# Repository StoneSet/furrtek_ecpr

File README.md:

# EPAR EMITTER HACK

## The Eagle project of the epar project + and modified firmware

**(c) Found the entire project here : http://furrtek.free.fr/?a=epar**

## For futher

As we know, only 350 cities (minimum), have been equipped with this system, (which makes 10% of the total cities in France in 2014). To have this famous cities code which is coded on 8 bits (so 255 possibilities), it is necessary to scan the frequencies 31MHz to 32MHz, which is tedious, this repo proposes to you a "brut-force", the program has been modified so that the 255 possibilities are tested. Once you have the code you can directly inform it in the remote control, it will go faster. This is just the theory, I have not tried it yet, but I would update this readme as soon as I have some pretty big breakthroughs.

## Included:

- All needed files to modify the project
- BOM (see in /pcb/)
- 🚧 Modified firmware (see in /firmware/) in WIP

## To use it :

1. Buy the pcb then solder every composants.
2. Flash the Atmega8 with *eparremote.hex* with these fuses :

- Low: *0xE4*, High: *0xD9*
## Some img's :

### To dot it, you will need :

| Components | list |
|--|--|
| x1 Atmega8 | x1 78L05 regulator |
| x1 10k potentiometer | x4 12mm switch |
| x1 0802 screen | x1 AD9850 |
| x1 10k resistor | x1 47uF capacitor |
| x1 100uH coil | x1 Green led |
| x1 1nF capacitor | x1 10nF capacitor |
| x1 BFR96 | x1 47k resistor |
| x1 SPDT switch | x1 FM antenna |
| x1 9v clip | x1 1N4001 diode |

Tested, it will work perfectly !

#

(c) @furrtek & @StoneSet & @lefuturiste - http://furrtek.free.fr/?a=esl - http://stoneset.github.io/ (2019)

plz do not steal, i'm not the owner of this project, i'm only the owner of this pcb. Have fun !

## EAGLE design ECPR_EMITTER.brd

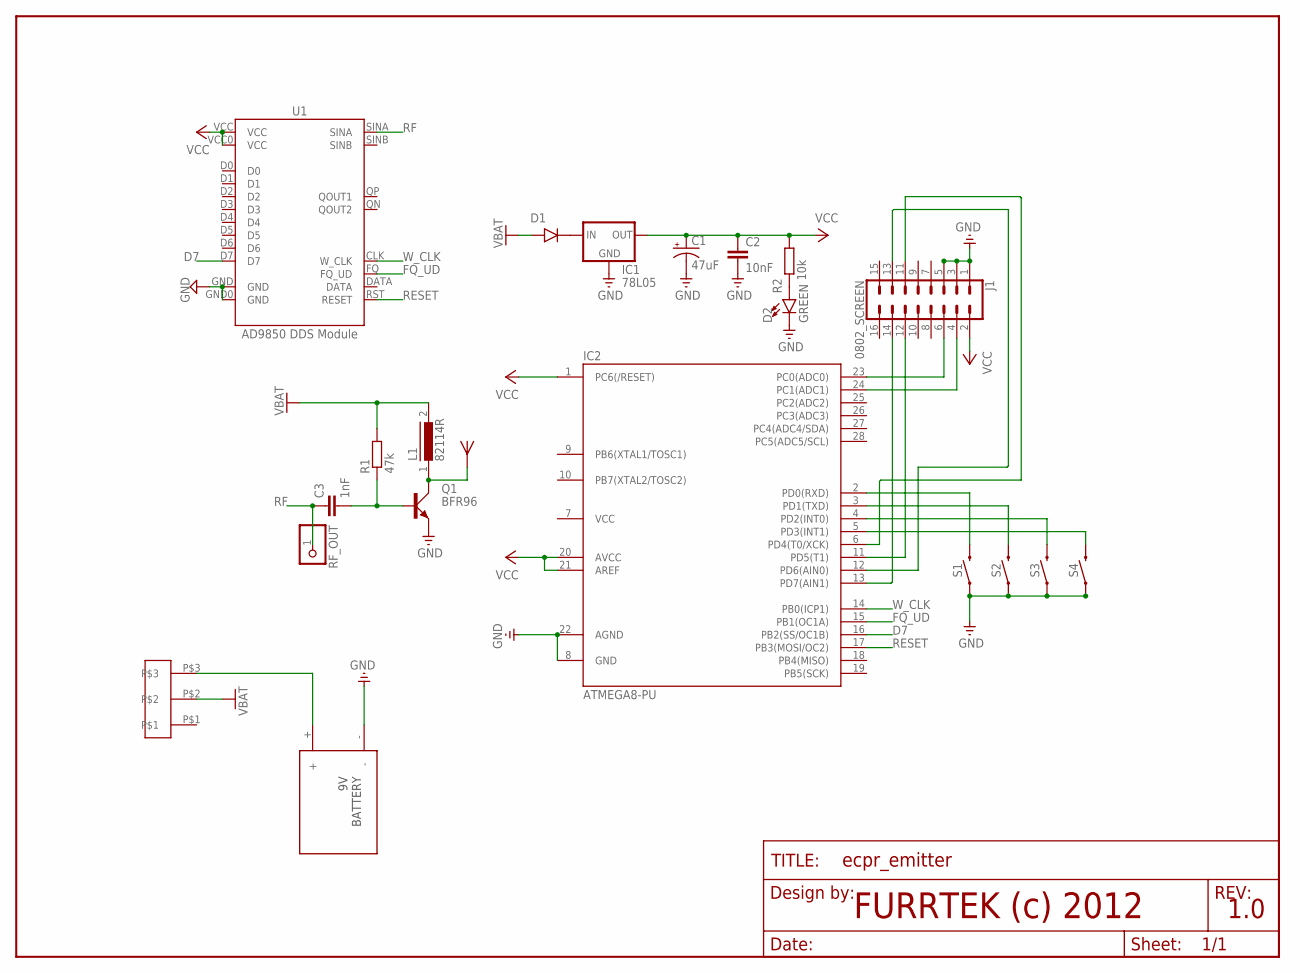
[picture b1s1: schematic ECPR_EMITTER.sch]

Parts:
C1: 47uF; CPOL-RADIAL-10UF-25V
C2: 10nF; CAP-PTH-10MM
C3: 1nF; C5B3
D1: 1N4001; DO41-10
D2: GREEN; LED_3MM-NS
FRAME1: FRAME-LETTERNO_PACKAGE; DUMMY
IC1: 78L05; 78XXL
IC2: ATMEGA8-PU; DIL28-3
J1: 0802_SCREEN; 2X8
L1: 82114R
Q1: BFR96; SOT37
R1: 47k; 0207/7
R2: 10k; 0207/7
RF_OUT: PINHD-1X1; 1X01
S1, S2, S3, S4: MOMENTARY-SWITCH-SPST-PTH-12MM; TACTILE_SWITCH_PTH_12MM
U1: AD9850 DDS Module; DDS_AD9850
U$1: ANT.; ANTENNA
U$2: PACKAGESWITCH; SLIDESWITCH
U$3: BAT

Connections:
D7: IC2.16 (PB2(SS/OC1B)), U1.D7
FQ_UD: IC2.15 (PB1(OC1A)), U1.FQ (FQ_UD)
GND: C1.2 (-), C2.2, D2.K (C), IC1.GND, IC2.8 (GND), IC2.22 (AGND), J1.1, J1.3, J1.5, Q1.2 (E), S1.1, S2.1, S3.1, S4.1, U1.GND, U1.GND0 (GND), U$3.-
unnamed: D1.C (CATHODE), IC1.IN
unnamed: C3.2, Q1.3 (B), R1.1
unnamed: IC2.2 (PD0(RXD)), S1.3 (2)
unnamed: IC2.3 (PD1(TXD)), S2.3 (2)
unnamed: IC2.4 (PD2(INT0)), S3.3 (2)
unnamed: IC2.5 (PD3(INT1)), S4.3 (2)
unnamed: L1.1, Q1.1 (C), U$1.ANT
unnamed: IC2.24 (PC1(ADC1)), J1.4
unnamed: IC2.23 (PC0(ADC0)), J1.6
unnamed: IC2.13 (PD7(AIN1)), J1.14
unnamed: IC2.11 (PD5(T1)), J1.12
unnamed: U$2.P$3, U$3.+
unnamed: IC2.12 (PD6(AIN0)), J1.13
unnamed: IC2.6 (PD4(T0/XCK)), J1.11
unnamed: D2.A, R2.1
RESET: IC2.17 (PB3(MOSI/OC2)), U1.RST (RESET)
RF: C3.1, RF_OUT.1, U1.SINA
VBAT: D1.A (ANODE), L1.2, R1.2, U$2.P$2
VCC: C1.1 (+), C2.1, IC1.OUT, IC2.1 (PC6(/RESET)), IC2.7 (VCC), IC2.20 (AVCC), IC2.21 (AREF), J1.2, R2.2, U1.VCC, U1.VCC0 (VCC)
W_CLK: IC2.14 (PB0(ICP1)), U1.CLK (W_CLK)

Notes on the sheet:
FURRTEK (c) 2012
1.0

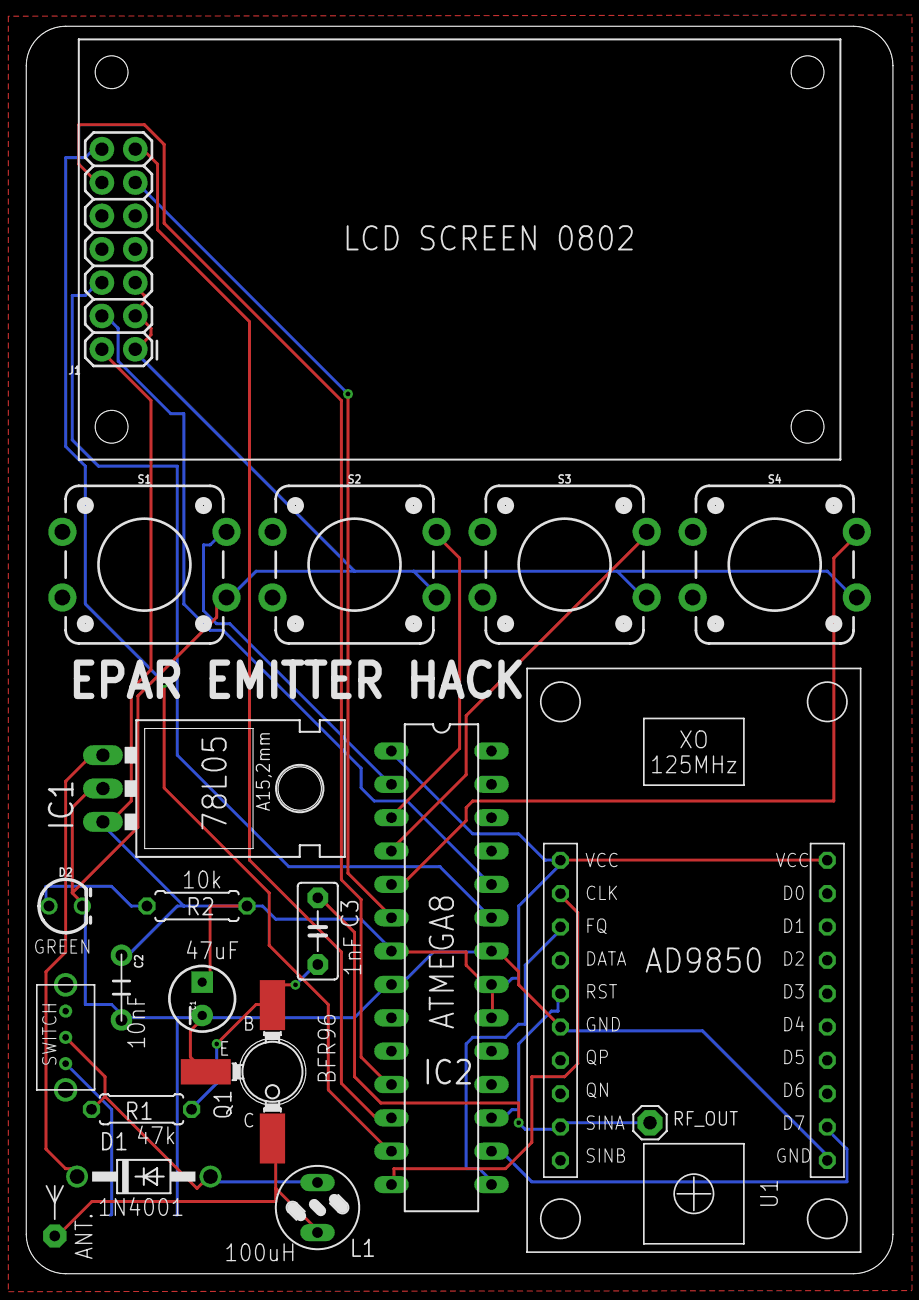
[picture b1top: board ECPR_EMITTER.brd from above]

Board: 2 copper layers, 66.0 x 95.0 mm, 22 parts (1 on the bottom side), 23 nets.

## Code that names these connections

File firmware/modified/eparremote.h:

#define PULLUPS 0b00001111

void com(uint8_t command);
void disp();
void cur_rel();
void cur_freq();
void cur_span();
void cur_code();
void cur_zone();
void wrt(const uint8_t *FlashLoc);
void EPAR_TX(uint8_t citycode, uint8_t zone, uint8_t relay, uint8_t state, uint8_t reverse, uint8_t rep);
void wrtr(char *cbuf);
void wrtc(char chr);
void Up();
void Down();
uint8_t hex(uint8_t num);

#define ZONE_A 0
#define ZONE_B 1
#define ZONE_C 2
#define ZONE_TP 3

#define RELAY1	1
#define RELAY2  0

#define OPEN 0
#define CLOSED 1

#define NORMAL 0
#define REVERSE 1

#define REPEAT 26

#define FREQ_MAX 40
#define FREQ_MIN 20

#define ECART_MAX 1
#define ECART_MIN 0.001

#define POWERDOWN 4

#define AD9850_W_CLK	PB0
#define AD9850_FQ_UD	PB1
#define AD9850_D7		PB2
#define AD9850_RESET	PB3

#define E	PC0
#define RS	PC1

enum MENUT {MENU_FREQ,MENU_SPAN,MENU_REL,MENU_CODE,MENU_ZONE,MENU_XMIT};

#define MENU_FIRST MENU_FREQ
#define MENU_LAST MENU_XMIT

const double power[6];

char test[8];

uint8_t editing,selected;
uint8_t reli,bitedit,digitedit;

uint8_t relay[2],menu;
double	fr;
uint8_t citycode;
uint8_t zone;
double ec;

uint8_t EEcode;
uint8_t EEzone;
uint8_t EEmenu;
uint32_t EEfr;
uint32_t EEec;

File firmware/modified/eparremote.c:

/*
Telecommande EPAR v1.1
07/10/2012 CC by Furrtek
ATMega8 8Mhz RC
*/

#define F_CPU 8000000UL

#include <avr/io.h>
#include <avr/interrupt.h>
#include <util/delay.h>
#include <stdlib.h>
#include <inttypes.h>
#include <avr/pgmspace.h>
#include <avr/eeprom.h>

#include "special.h"
#include "lcd.h"
#include "eparremote.h"
#include "navig.h"

typedef void (*FuncPtr)();
FuncPtr FPtr;

uint8_t editing=0;		// Bool valeur en edition
uint8_t selected=0;		// Bool chiffre choisi
uint8_t reli=0;			// # relais en edition
uint8_t bitedit=0;		// # bit en edition
uint8_t digitedit=0;	// # chiffre en edition

uint8_t relay[2] = {0,0};	// Etat relais
uint8_t menu = MENU_CODE;	// Menu (au demarrage)
double fr;					// Valeur frequence centrale (MHz)
double ec;					// Valeur ecart frequence (MHz)
uint8_t citycode;
uint8_t zone;

uint8_t EEMEM EEcode;		// Sauvegardes en EEPROM
uint8_t EEMEM EEzone;
uint8_t EEMEM EEmenu;
uint32_t EEMEM EEfr;
uint32_t EEMEM EEec;

const uint8_t fwa[] PROGMEM = "TLC EPAR";	// Splash pour se la peter
const uint8_t fwb[] PROGMEM = "Ver. 1.1";
const uint8_t fwc[] PROGMEM = "Furrtek\"";
const uint8_t fwd[] PROGMEM = "07/10/12";

// Table de handlers pour les menus
const FuncPtr FTableEditing[] PROGMEM = {FE_DIGIT,FE_DIGIT,FE_REL,FE_CODE,FE_ZONE,FE_XMIT};
const FuncPtr FTableChoose[] PROGMEM = {FC_FREQ,FC_SPAN,FC_REL,FC_CODE,FC_ZONE,FC_XMIT};
const FuncPtr FTableLeftEditing[] PROGMEM = {FLE_FREQ,FLE_SPAN,FLE_REL,FLE_CODE,FLE_ZONE,FLE_XMIT};
const FuncPtr FTableRightEditing[] PROGMEM = {FRE_FREQ,FRE_SPAN,FRE_REL,FRE_CODE,FRE_ZONE,FRE_XMIT};
const FuncPtr FTableDisp[] PROGMEM = {FD_FREQ,FD_SPAN,FD_REL,FD_CODE,FD_ZONE,FD_XMIT};
const FuncPtr FTableSave[] PROGMEM = {FS_FREQ,FS_SPAN,FS_REL,FS_CODE,FS_ZONE,FS_XMIT};

const double power[6] = {0.0001,0.001,0.01,0.1,1,10};	// Puissances de 10

void disp() {
	// MAJ affichage LCD
	FPtr=(FuncPtr)pgm_read_word(&FTableDisp[menu]);
	FPtr();
}

int main(void) {
	WDTCR = (1<<WDCE) | (1<<WDE);	// Watchdog off (dangereux)
	WDTCR = 0x00;

	DDRB = 0b00001111;	// Outputs vers AD9850
	DDRD = 0b11110000;	// Data LCD
	DDRC = 0b00000011;	// Control LCD

	PORTD = 0b00100000 | PULLUPS;	// Mode 8 bits
	_delay_us(100);
	PORTC |= _BV(E);
	_delay_us(100);
	PORTC &= ~_BV(E);
	_delay_us(100);

	com(0b00101000);		// 2 lignes
	com(0b00000001);		// Clear
	com(0b00000010);		// Home
	com(0b00001100);		// Ecran on, cursor off, blink off

	com(0b10000000);		// Ligne 1
	wrt(fwa);
	com(0b11000000);		// Ligne 2
	wrt(fwb);

	_delay_ms(1000);

	com(0b10000000);		// Ligne 1
	wrt(fwc);
	com(0b11000000);		// Ligne 2
	wrt(fwd);

	_delay_ms(1000);

	PORTB = _BV(AD9850_RESET);	// Init mode serie AD9850
	_delay_ms(100);
	PORTB = 0;
	_delay_ms(100);

	PORTB = _BV(AD9850_W_CLK);
	_delay_ms(1);
	PORTB = 0;
	_delay_ms(1);

	PORTB = _BV(AD9850_FQ_UD);
	_delay_ms(1);
	PORTB = 0;
	_delay_ms(1);

	update(0,POWERDOWN);	// DDS au dodo

	// Recup sauvegarde EEPROM + sanitizing
	//menu = eeprom_read_byte(&EEmenu);
	//if (menu > MENU_LAST) menu = MENU_FIRST;
	citycode = eeprom_read_byte(&EEcode);
	zone = eeprom_read_byte(&EEzone);
	if (zone > 3) zone = 3;

	eeprom_read_block((void*)&ec, (const void*)&EEec, sizeof(double));
	if ((((*(uint32_t*)&ec) & 0x7fffffff) > 0x7f800000)||(ec < ECART_MIN)||(ec > ECART_MAX)) ec = 0.003;
	eeprom_read_block((void*)&fr, (const void*)&EEfr, sizeof(double)); 
	if ((((*(uint32_t*)&fr) & 0x7fffffff) > 0x7f800000)||(fr < FREQ_MIN)||(fr > FREQ_MAX)) fr = 31;

	disp();

	for (;;) {
		while ((PIND & PULLUPS) == PULLUPS) {};
		_delay_ms(50);
		if (!bit_is_set(PIND,PD0)) {
			// Gauche
			while(!bit_is_set(PIND,PD0)) {};
			if (editing) {
				// Modif valeur
				FPtr=(FuncPtr)pgm_read_word(&FTableLeftEditing[menu]);
				FPtr();
			} else {
				// Menu precedent
				if (menu == MENU_FIRST) {
					menu = MENU_LAST;
				} else {
					menu--;
				}
				disp();
			}
		} else if (!bit_is_set(PIND,PD3)) {
			// Droite
			while(!bit_is_set(PIND,PD3)) {};
			if (editing) {
				// Modif valeur
				FPtr=(FuncPtr)pgm_read_word(&FTableRightEditing[menu]);
				FPtr();
			} else {
				// Menu suivant
				if (menu == MENU_LAST) {
					menu = MENU_FIRST;
				} else {
					menu++;
				}
				disp();
			}
		} else if (!bit_is_set(PIND,PD1)) {
			// Edition
			while(!bit_is_set(PIND,PD1)) {};
			if (editing) {
				// Modif valeur
				FPtr=(FuncPtr)pgm_read_word(&FTableEditing[menu]);
				FPtr();
			} else {
				// Selection valeur
				eeprom_write_byte(&EEmenu,menu);
				editing = 1;
				digitedit = 0;
				FPtr=(FuncPtr)pgm_read_word(&FTableChoose[menu]);
				FPtr();
			}
		} else if (!bit_is_set(PIND,PD2)) {
			// Validation
			while(!bit_is_set(PIND,PD2)) {};
			editing = 0;
			selected = 0;
			com(0b00001100);		// blink et cursor off
			FPtr=(FuncPtr)pgm_read_word(&FTableSave[menu]);
			FPtr();
		}
	}

  return 0;
}

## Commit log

2017-09-06 First release (Yay!)
    yay
2019-04-22 feat(pcb): add eagle project w/ :
    - BOM
    - img
    - zip of furrtek website
    - all libs
    - gerber
2019-04-22 wip: feat(readme): add new version of the readme
2019-04-22 feat(readme): add embed youtube videos in readme
2019-04-22 fix(readme): no html plz
2019-04-22 feat(board): final version w/ led, switch, pads for battery, rf connected, new version of AD9850 libs
2019-04-23 feat(button): move button to the top
2019-04-24 feat(testpin): add rf out and update to eagle 9.4.0
2019-04-24 feat(pcb): add rounded corners to the pcb
2019-06-10 fix repo name
2019-06-12 fix: screen orientation & pin23/24
2019-06-13 FUCK
2019-07-01 WIP feat: modified firmware (nothing at this time, but u should wait)
    be patient
2019-08-07 feat(refactor): big refactoring & new readme
    modified firmware in WIP
2019-09-08 fix(readme): add gif & more
2019-09-08 test readme gif
2019-09-08 readme test
2019-09-08 readme test 2

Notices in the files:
ECPR_EMITTER.brd:
CREATED BY FURRTEK (c) 2012
parts and their libraries:
SparkFun-Capacitors: Licensing: Creative Commons ShareAlike 4.0 International - https://creativecommons.org/licenses/by-sa/4.0
computronics.com.au: ©Computronics Corporation Ltd, 2004
supply0: Copyright (C) 2007, Bob Starr
SparkFun-Aesthetics: https://creativecommons.org/licenses/by-sa/4.0
